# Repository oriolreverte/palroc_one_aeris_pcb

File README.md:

<h1 align="center">aeris_pcb</h1>

<p align="center" width="100%">
  
</p>

***

<p align="center">
  
&nbsp; &nbsp; &nbsp; &nbsp;
  
</p>

***

## SPECIFICATIONS

| Parameter | Value | 
| --- | --- |
| Dimensions | 102.5 × 90.0 mm |

***

## DIRECTORY STRUCTURE

    .
    ├─ Computations       # Misc calculations
    ├─ HTML               # HTML files for generated webpage
    ├─ Images             # Pictures and renders
    │
    ├─ kibot_resources    # External resources for KiBot
    │  ├─ colors          # Color theme for KiCad
    │  ├─ fonts           # Fonts used in the project
    │  ├─ scripts         # External scripts used with KiBot
    │  └─ templates       # Templates for KiBot generated reports
    │
    ├─ kibot_yaml         # KiBot YAML config files
    ├─ KiRI               # KiRI (PCB diff viewer) files
    │
    ├─ lib                # KiCad footprint and symbol libraries
    │  ├─ 3d_models       # Component 3D models
    │  ├─ lib_fp          # Footprint libraries
    │  └─ lib_sym         # Symbol libraries
    │
    ├─ Logos              # Logos
    │
    ├─ Manufacturing      # Assembly and fabrication documents
    │  ├─ Assembly        # Assembly documents (BoM, pos, notes)
    │  │
    │  └─ Fabrication     # Fabrication documents (ZIP, notes)
    │     ├─ Drill Tables # CSV drill tables
    │     └─ Gerbers      # Gerbers
    │
    ├─ Report             # Reports for ERC/DRC
    ├─ Schematic          # PDF of schematic
    ├─ Templates          # Title block templates
    ├─ Testing
    │  └─ Testpoints      # Testpoints tables      
    │
    └─ Variants           # Outputs for assembly variants

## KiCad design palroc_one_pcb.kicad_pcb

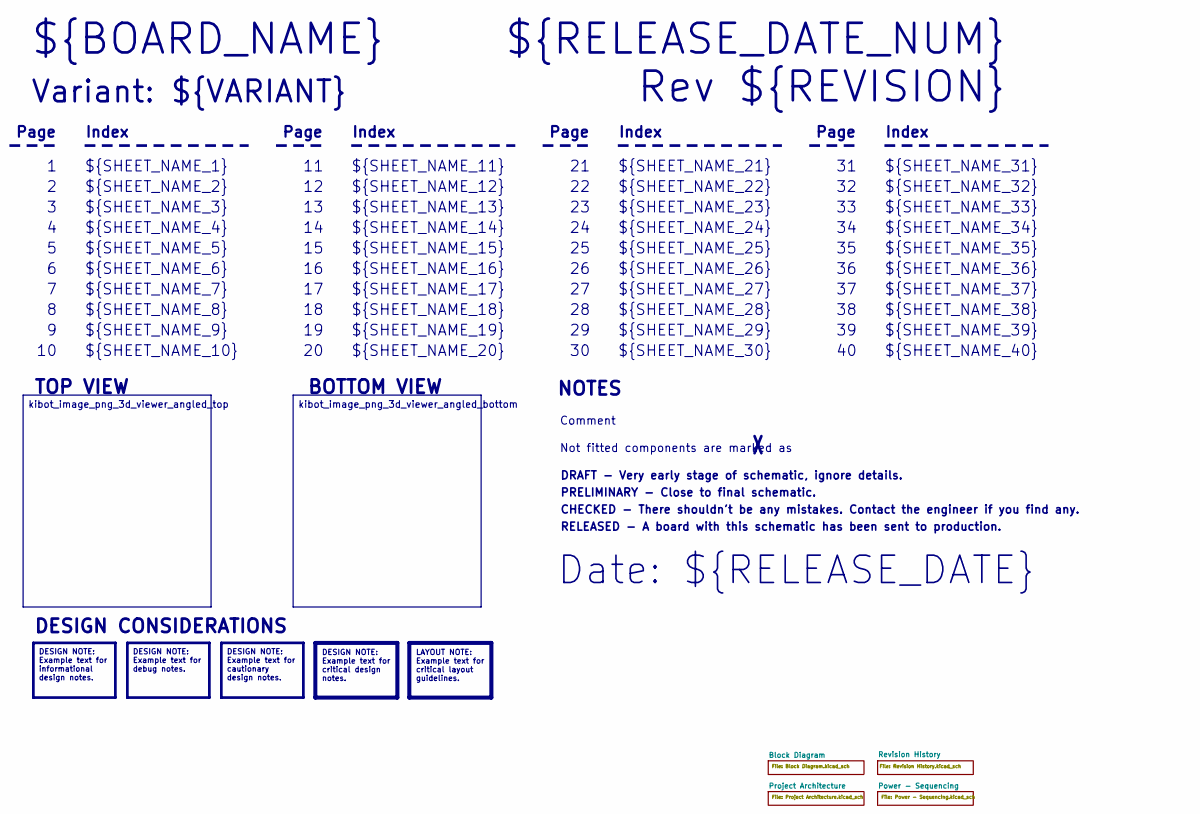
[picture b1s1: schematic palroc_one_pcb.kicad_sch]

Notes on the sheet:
Variant: ${VARIANT}
RELEASED - A board with this schematic has been sent to production.
${SHEET_NAME_24}
Index
Page
PRELIMINARY - Close to final schematic.
${SHEET_NAME_22}
DRAFT - Very early stage of schematic, ignore details.
${SHEET_NAME_12}
${SHEET_NAME_8}
${SHEET_NAME_2}
${SHEET_NAME_5}
${SHEET_NAME_20}
${SHEET_NAME_23}
${RELEASE_DATE_NUM}
${SHEET_NAME_35}
Not fitted components are marked as
${SHEET_NAME_11}
${SHEET_NAME_6}
${SHEET_NAME_37}
${SHEET_NAME_26}
${SHEET_NAME_36}
Rev ${REVISION}
${SHEET_NAME_15}
CHECKED - There shouldn't be any mistakes. Contact the engineer if you find any.
BOTTOM VIEW
${SHEET_NAME_14}
${SHEET_NAME_21}
${SHEET_NAME_17}
${SHEET_NAME_18}
Date: ${RELEASE_DATE}
${SHEET_NAME_7}
${SHEET_NAME_31}
${BOARD_NAME}
NOTES
${SHEET_NAME_40}
${SHEET_NAME_39}
${SHEET_NAME_32}
${SHEET_NAME_1}
${SHEET_NAME_9}

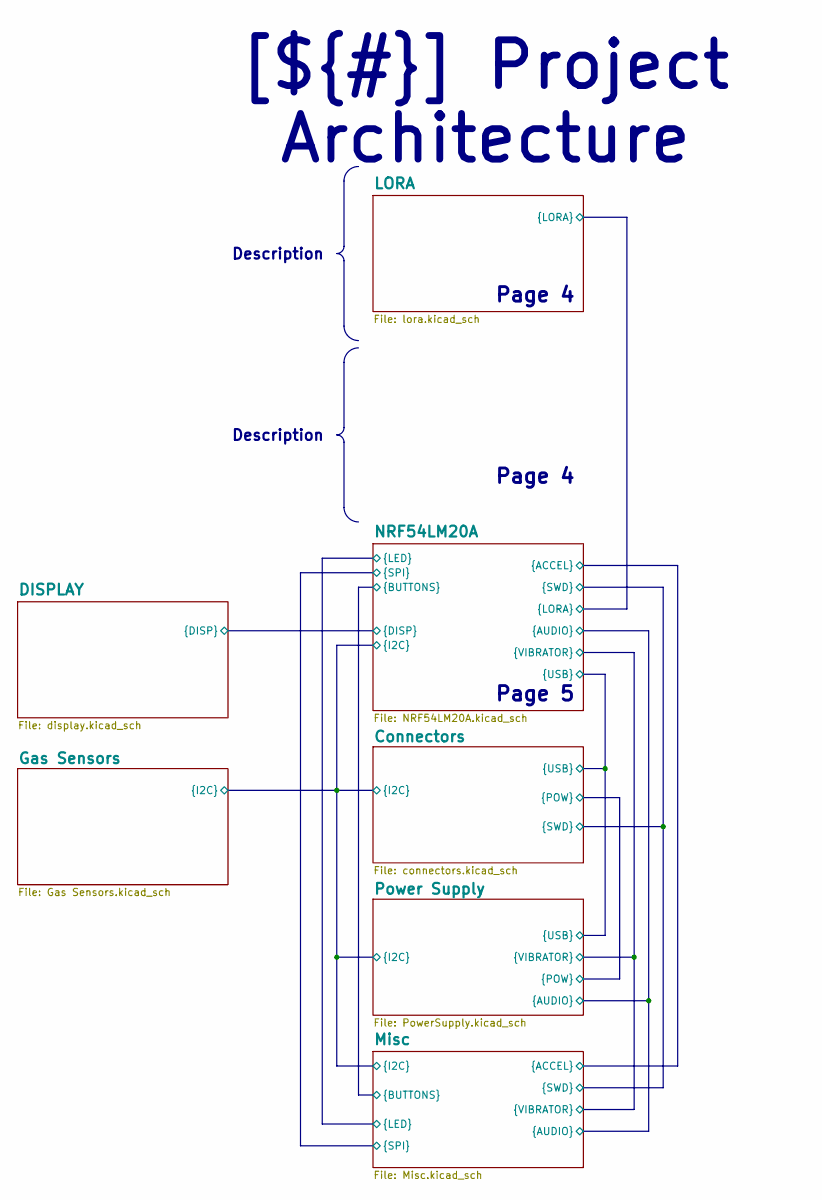
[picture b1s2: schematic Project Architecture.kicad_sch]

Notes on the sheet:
Page 4
Page 5
Description
[${#}] ${TITLE}

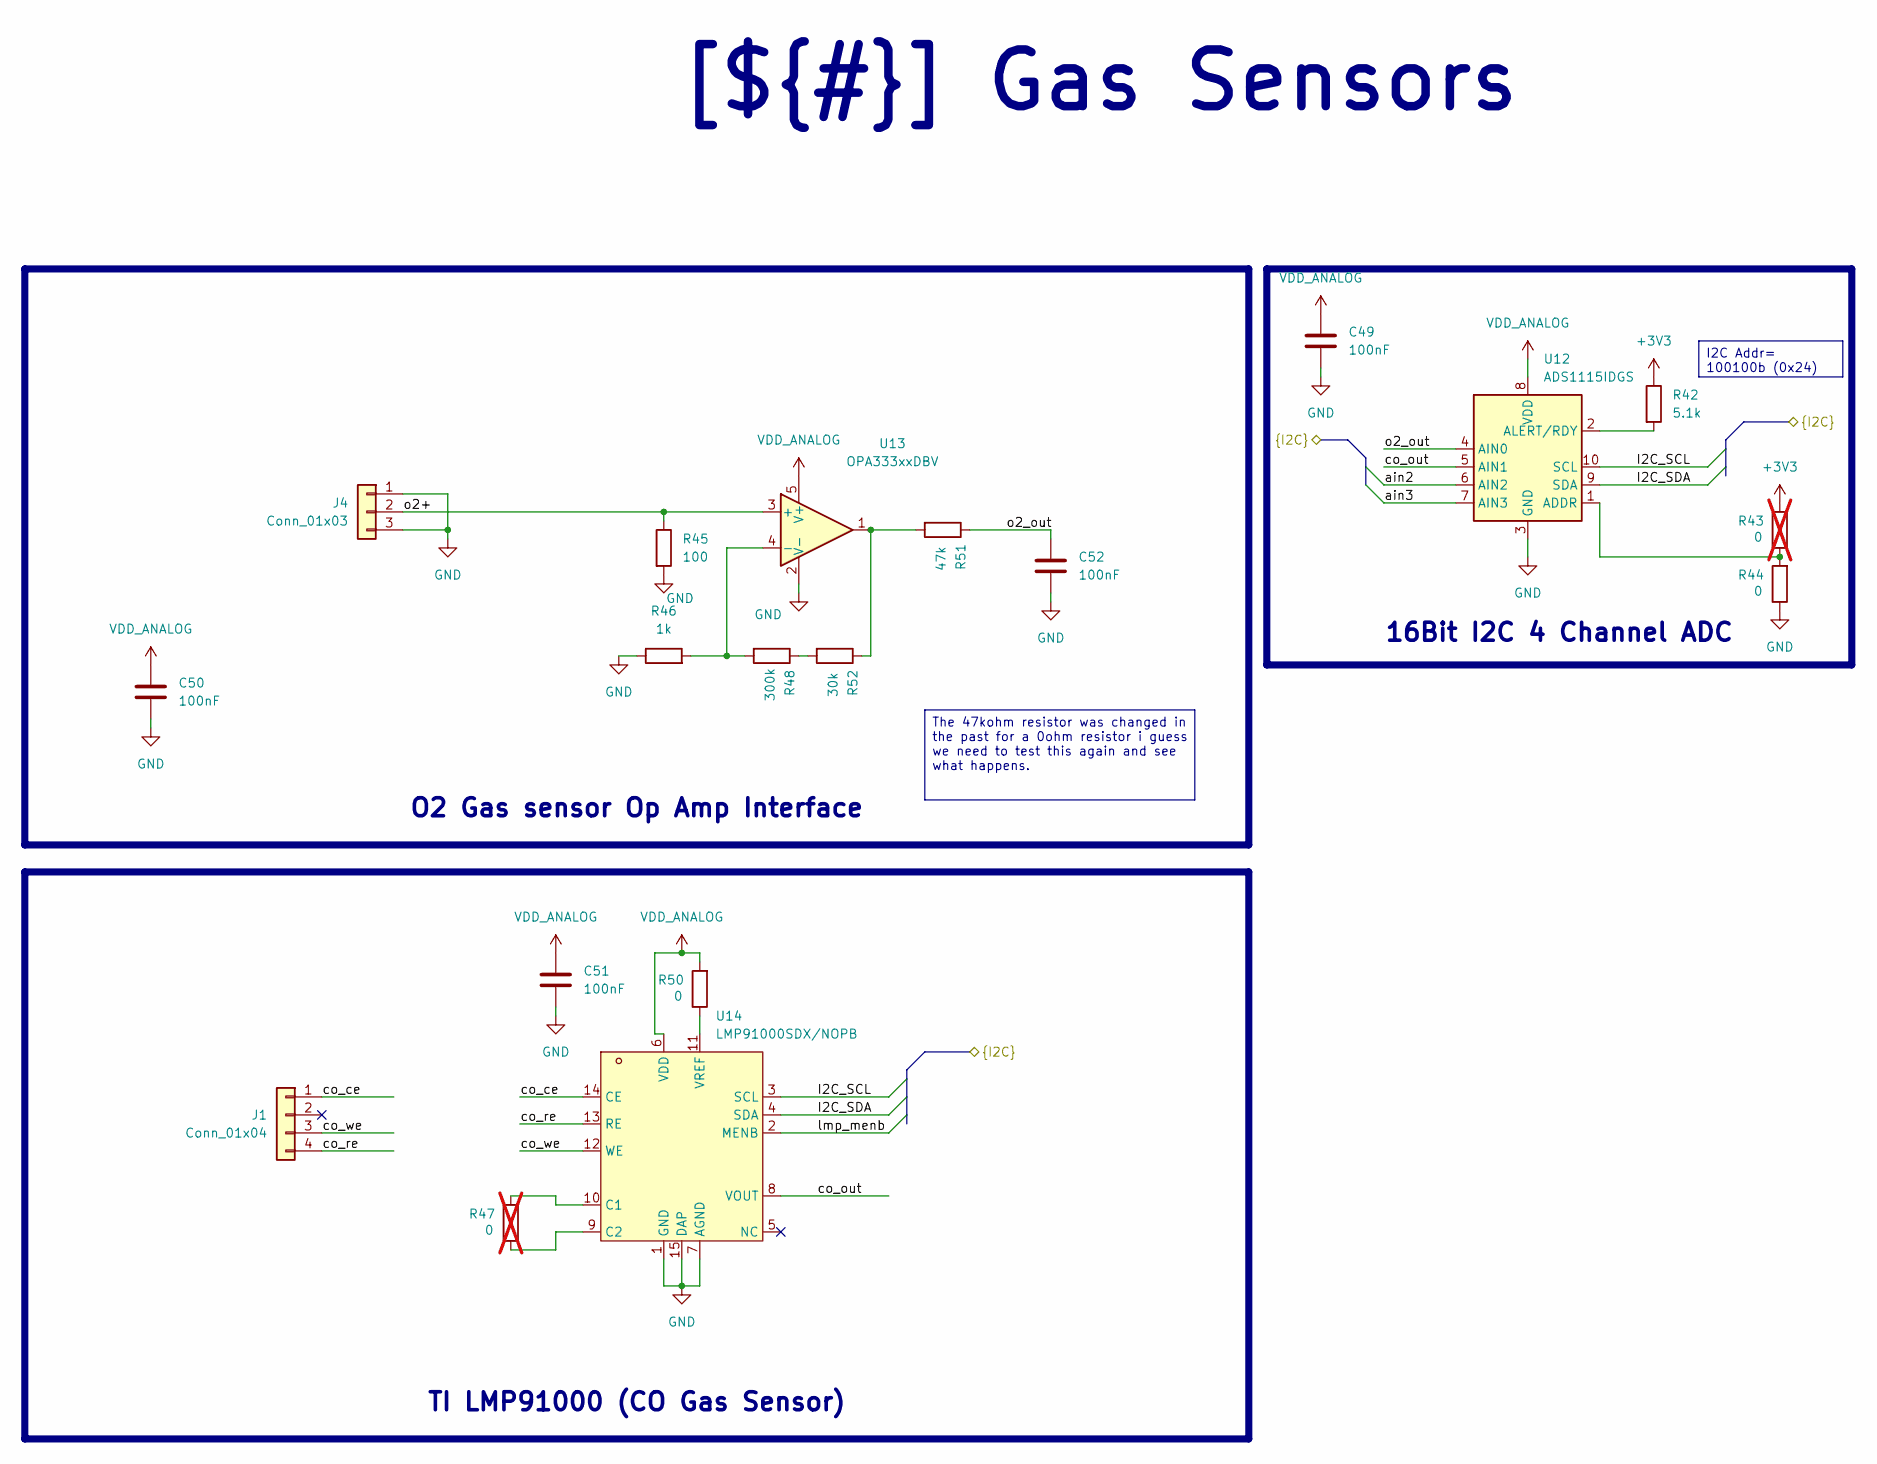
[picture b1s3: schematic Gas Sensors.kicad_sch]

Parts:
C49, C50, C51, C52: 100nF; c_0402_nordic; LCSC C1525
J1: Conn_01x04; 0294-0-15-80-06-80-10-0_co-d4
J4: Conn_01x03; 0364-0-15-80-13-80-10-0_o2-g2
R42: 5.1k; r_0402_nordic; LCSC C25905
R43, R47: 0; r_0402_nordic; Manufacturer Part Number ERJ-2GE0R00X; LCSC C242160; not fitted
R44, R50: 0; r_0402_nordic; Manufacturer Part Number ERJ-2GE0R00X; LCSC C242160
R45: 100; r_0402_nordic; LCSC C25076
R46: 1k; r_0402_nordic; LCSC C11702
R48: 300k; r_0402_nordic; Manufacturer Part Number 0402WGF3003TCE; LCSC C25774
R51: 47k; r_0402_nordic; LCSC C25792
R52: 30k; r_0603_nordic; LCSC C22984
U12: ADS1115IDGS; TSSOP-10_3x3mm_P0.5mm; LCSC C37593
U13: OPA333xxDBV; SOT-23-5
U14: LMP91000SDX/NOPB; WSON-14_L4.0-W4.0-P0.50-BL-EP-1; LCSC Part C2651584

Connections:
+3V3: R42.1, R43.2; also elsewhere on the board
/Project Architecture/Connectors/I2C_SCL: U12.10 (SCL), U14.3 (SCL); also elsewhere on the board
/Project Architecture/Connectors/I2C_SDA: U12.9 (SDA), U14.4 (SDA); also elsewhere on the board
/Project Architecture/Gas Sensors/ain2: U12.6 (AIN2)
/Project Architecture/Gas Sensors/ain3: U12.7 (AIN3)
/Project Architecture/Gas Sensors/co_ce: J1.1, U14.14 (CE)
/Project Architecture/Gas Sensors/co_out: U12.5 (AIN1), U14.8 (VOUT)
/Project Architecture/Gas Sensors/co_re: J1.4, U14.13 (RE)
/Project Architecture/Gas Sensors/co_we: J1.3, U14.12 (WE)
/Project Architecture/Gas Sensors/lmp_menb: U14.2 (MENB)
/Project Architecture/Gas Sensors/o2+: J4.2, R45.1, U13.3 (+)
/Project Architecture/Gas Sensors/o2_out: C52.1, R51.1, U12.4 (AIN0)
GND: C49.2, C50.2, C51.2, C52.2, J4.1, J4.3, R44.1, R45.2, R46.1, U12.3 (GND), U13.2 (V-), U14.1 (GND), U14.7 (AGND), U14.15 (DAP); also elsewhere on the board
unnamed: R48.1, R52.2
unnamed: R51.2, R52.1, U13.1
unnamed: R43.1, R44.2, U12.1 (ADDR)
unnamed: R42.2, U12.2 (ALERT/RDY)
unnamed: R46.2, R48.2, U13.4 (-)
unnamed: R47.2, U14.10 (C1)
unnamed: R47.1, U14.9 (C2)
unnamed: R50.1, U14.11 (VREF)
VDD_ANALOG: C49.1, C50.1, C51.1, R50.2, U12.8 (VDD), U13.5 (V+), U14.6 (VDD); also elsewhere on the board

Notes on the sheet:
16Bit I2C 4 Channel ADC
I2C Addr= 100100b (0x24)
[${#}] ${TITLE}
The 47kohm resistor was changed in the past for a 0ohm resistor i guess we need to test this again and see what happens.
TI LMP91000 (CO Gas Sensor)
O2 Gas sensor Op Amp Interface

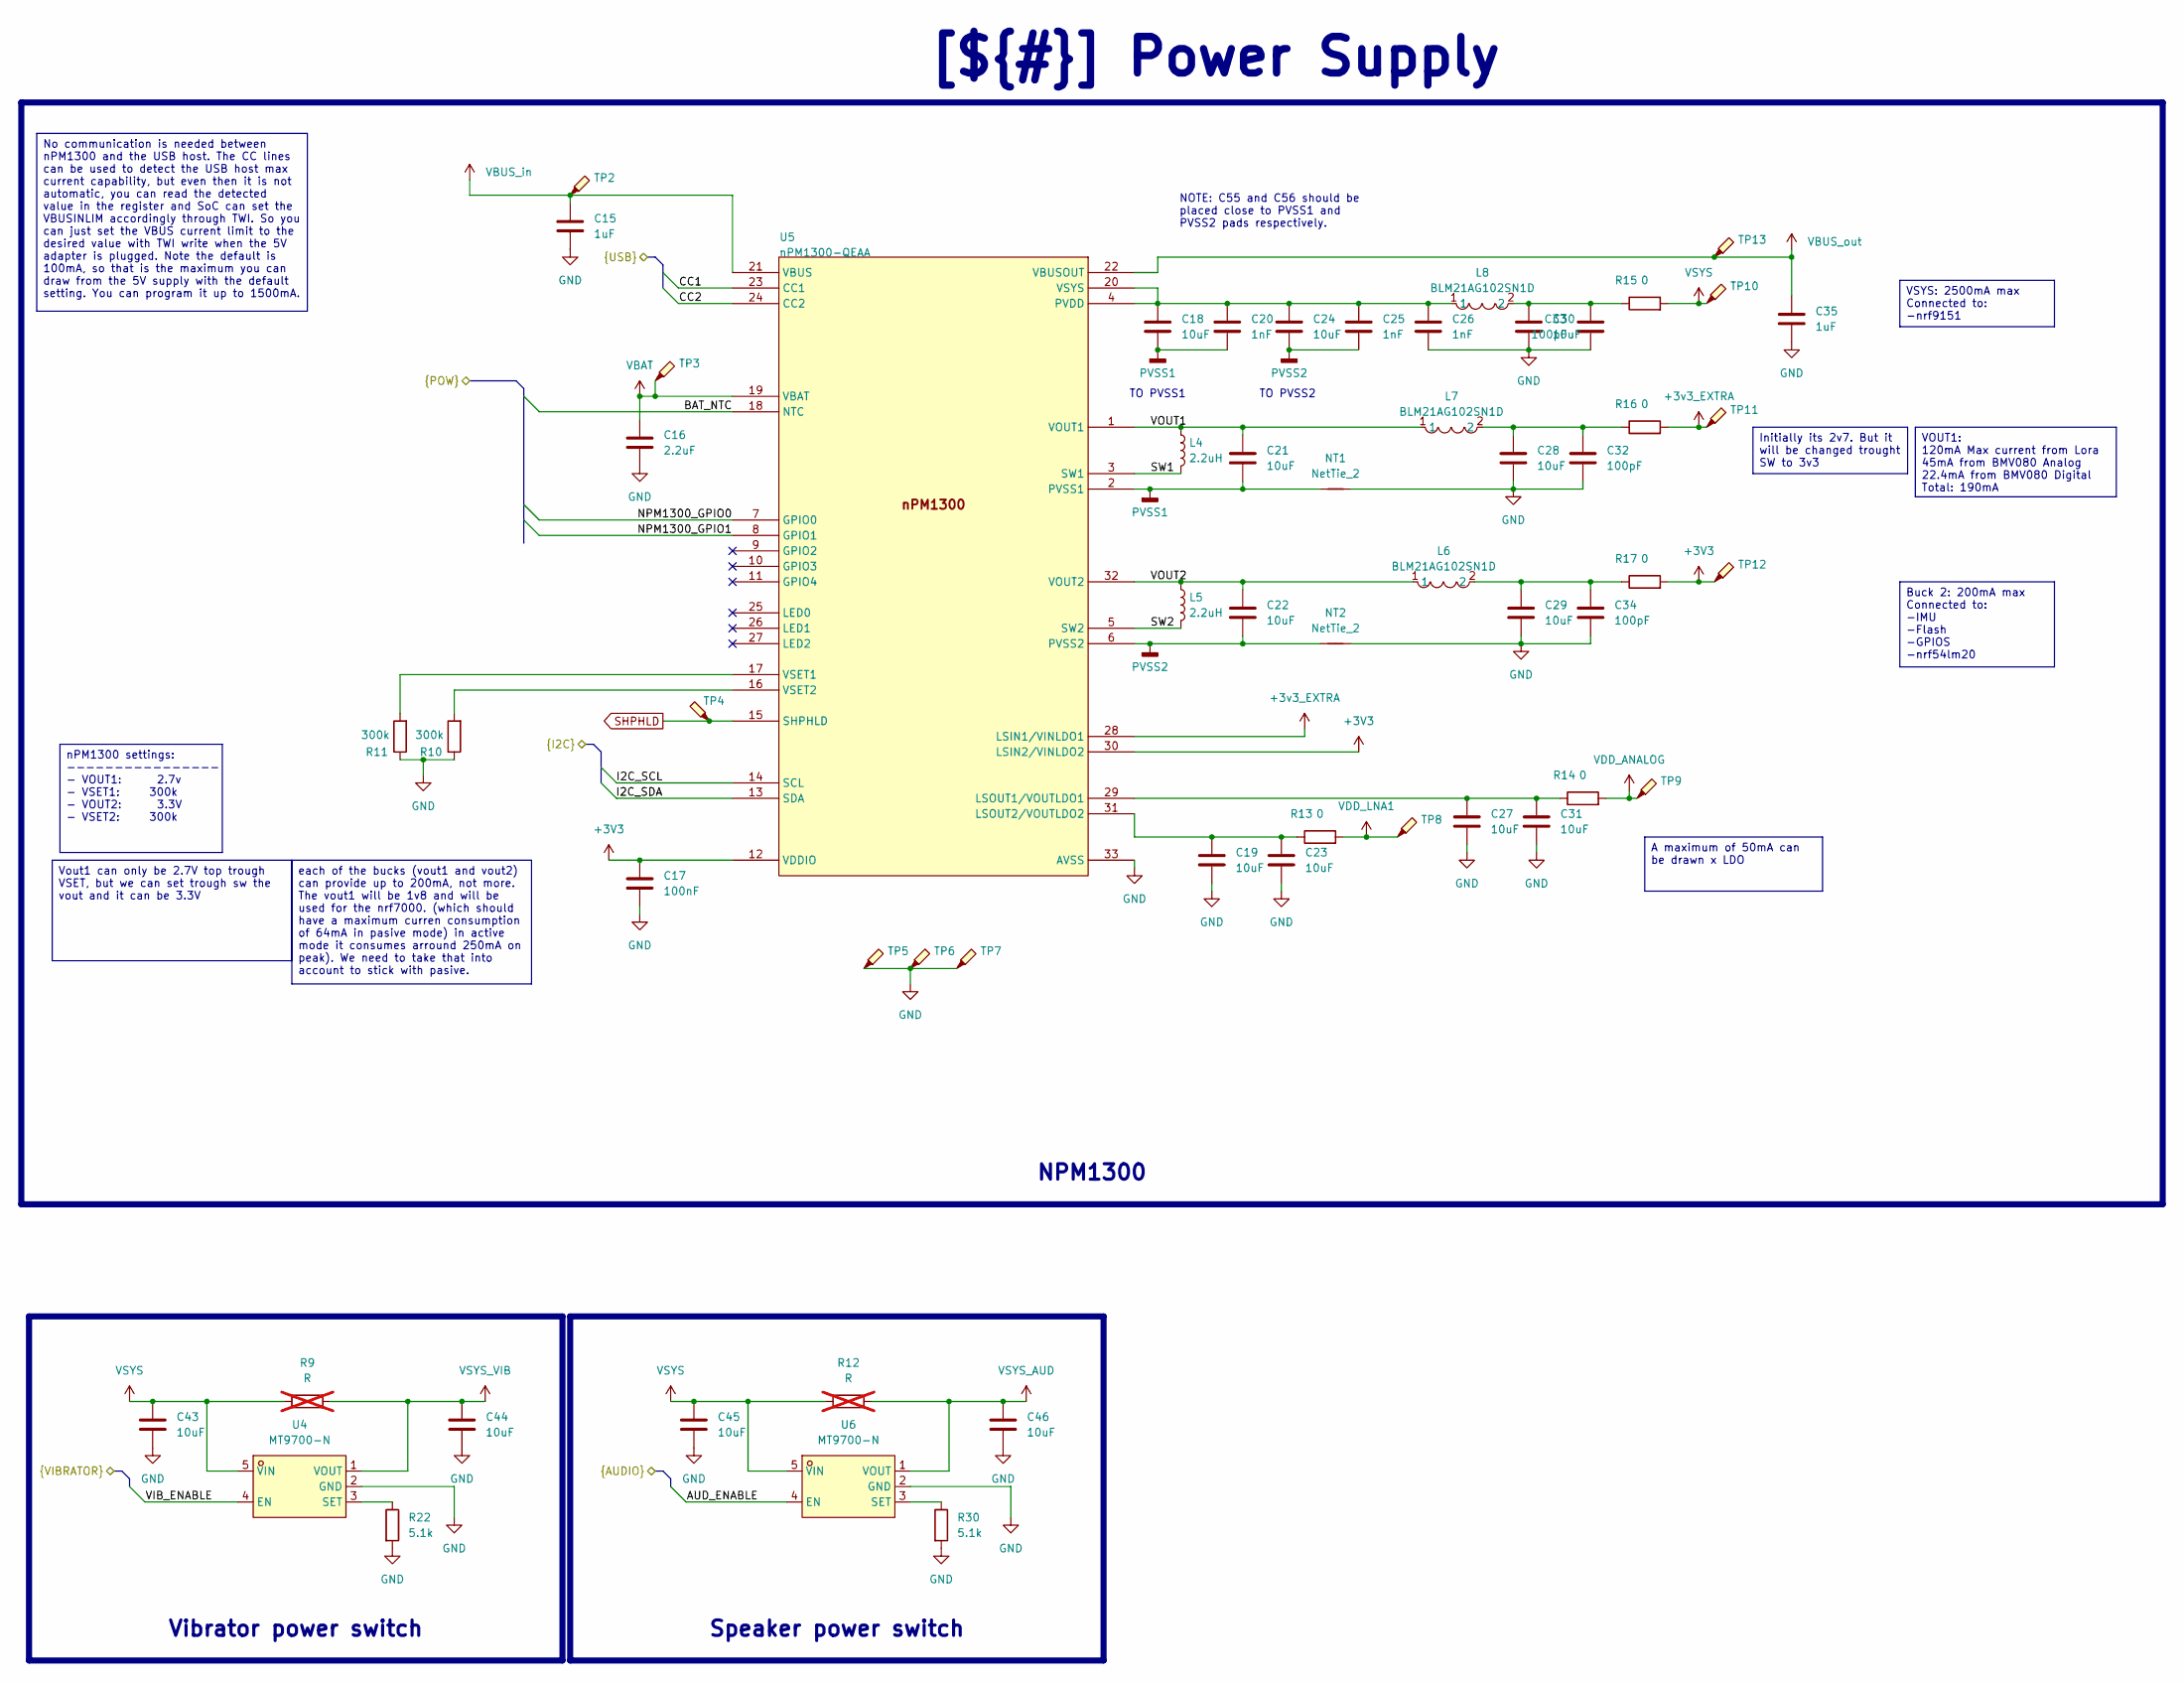
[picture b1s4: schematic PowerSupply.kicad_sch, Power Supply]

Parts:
C15, C35: 1uF; c_0402_nordic; Manufacturer Part Number CL05A105KA5NQNC; LCSC C52923
C16: 2.2uF; c_0402_nordic; Manufacturer Part Number CL05A225KO5NQNC; LCSC C170151
C17: 100nF; c_0201_nordic; Manufacturer Part Number CGA0201X5R104K100ET
C18, C24: 10uF; c_0603_nordic; Manufacturer Part Number CL10A106KP8NNNC; LCSC C19702
C19, C21, C22, C23, C27, C28, C29, C30, C31: 10uF; c_0402_nordic; Manufacturer Part Number CL05A106MP5NUNC; LCSC C315248
C20, C25, C26: 1nF; c_0201_nordic; Manufacturer Part Number CC0201KRX7R8BB102; LCSC C272854
C32, C33, C34: 100pF; c_0201_nordic; Manufacturer Part Number GRM0335C1E101GA01D
C43, C44, C45, C46: 10uF; c_0603_nordic; LCSC C19702
L4, L5: 2.2uH; l_0806_nordic; Manufacturer Part Number DFE201610E-2R2M=P2; LCSC C337891
L6, L7, L8: BLM21AG102SN1D; L0805; LCSC Part C85835
NT1, NT2: NetTie_2; NetTie-PALROC-viamm
R9, R12: R; r_0603_nordic; not fitted
R10, R11: 300k; r_0402_nordic; Manufacturer Part Number 0402WGF3003TCE; LCSC C25774
R13, R14, R15, R16, R17: 0; r_0402_nordic; Manufacturer Part Number ERJ-2GE0R00X; LCSC C242160
R22, R30: 5.1k; r_0402_nordic; LCSC C25905
TP2, TP3, TP4, TP5, TP6, TP7, TP8, TP9, TP10, TP11, TP12, TP13: TestPoint_Probe; TestPoint_Pad_D1.0mm
U4, U6: MT9700-N; SOT-23-5_L2.9-W1.6-P0.95-LS2.9-BL; MPN MT9700-N; LCSC Part C42441843
U5: nPM1300-QEAA; Nordic_QFN50P500X500X90-33N; PART NUMBER nPM1300-QEAA

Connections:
+3V3: C17.1, R17.2, TP12.1, U5.12 (VDDIO), U5.30 (LSIN2/VINLDO2); also elsewhere on the board
+3v3_EXTRA: R16.2, TP11.1, U5.28 (LSIN1/VINLDO1); also elsewhere on the board
/Project Architecture/Connectors/BAT_NTC: U5.18 (NTC); also elsewhere on the board
/Project Architecture/Connectors/CC1: U5.23 (CC1); also elsewhere on the board
/Project Architecture/Connectors/CC2: U5.24 (CC2); also elsewhere on the board
/Project Architecture/Connectors/I2C_SCL: U5.14 (SCL); also elsewhere on the board
/Project Architecture/Connectors/I2C_SDA: U5.13 (SDA); also elsewhere on the board
/Project Architecture/Misc/AUD_ENABLE: U6.4 (EN); also elsewhere on the board
/Project Architecture/Misc/VIB_ENABLE: U4.4 (EN); also elsewhere on the board
/Project Architecture/Power Supply/NPM1300_GPIO0: U5.7 (GPIO0)
/Project Architecture/Power Supply/NPM1300_GPIO1: U5.8 (GPIO1)
/Project Architecture/Power Supply/SW1: L4.2, U5.3 (SW1)
/Project Architecture/Power Supply/SW2: L5.2, U5.5 (SW2)
/Project Architecture/Power Supply/VOUT1: C21.1, L4.1, L7.1, U5.1 (VOUT1)
/Project Architecture/Power Supply/VOUT2: C22.1, L5.1, L6.1, U5.32 (VOUT2)
GND: C15.2, C16.2, C17.2, C19.2, C23.2, C26.2, C27.2, C28.2, C29.2, C30.2, C31.2, C32.2, C33.2, C34.2, C35.2, C43.2, C44.2, C45.2, C46.2, NT1.2, NT2.2, R10.1, R11.1, R22.2, R30.2, TP5.1, TP6.1, TP7.1, U4.2 (GND), U5.33 (AVSS), U6.2 (GND); also elsewhere on the board
unnamed: C28.1, C32.1, L7.2, R16.1
unnamed: C29.1, C34.1, L6.2, R17.1
unnamed: C30.1, C33.1, L8.2, R15.1
unnamed: R22.1, U4.3 (SET)
unnamed: C27.1, C31.1, R14.1, U5.29 (LSOUT1/VOUTLDO1)
unnamed: C19.1, C23.1, R13.1, U5.31 (LSOUT2/VOUTLDO2)
unnamed: C18.1, C20.1, C24.1, C25.1, C26.1, L8.1, U5.4 (PVDD), U5.20 (VSYS)
unnamed: R11.2, U5.17 (VSET1)
unnamed: R10.2, U5.16 (VSET2)
unnamed: R30.1, U6.3 (SET)
PVSS1: C18.2, C20.2, C21.2, NT1.1, U5.2 (PVSS1)
PVSS2: C22.2, C24.2, C25.2, NT2.1, U5.6 (PVSS2)
SHPHLD: TP4.1, U5.15 (SHPHLD); also elsewhere on the board
VBAT: C16.1, TP3.1, U5.19 (VBAT); also elsewhere on the board
VBUS_in: C15.1, TP2.1, U5.21 (VBUS); also elsewhere on the board
VBUS_out: C35.1, TP13.1, U5.22 (VBUSOUT); also elsewhere on the board
VDD_ANALOG: R14.2, TP9.1; also elsewhere on the board
VDD_LNA1: R13.2, TP8.1
VSYS: C43.1, C45.1, R9.1, R12.1, R15.2, TP10.1, U4.5 (VIN), U6.5 (VIN); also elsewhere on the board
VSYS_AUD: C46.1, R12.2, U6.1 (VOUT); also elsewhere on the board
VSYS_VIB: C44.1, R9.2, U4.1 (VOUT); also elsewhere on the board

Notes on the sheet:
TO PVSS1
TO PVSS2
No communication is needed between nPM1300 and the USB host. The CC lines can be used to detect the USB host max current capability, but even then it is not automatic, you can read the detected value in the register and SoC can set the VBUSINLIM accordingly through TWI. So you can just set the VBUS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
[${#}] ${TITLE}
VSYS: 2500mA max Connected to: -nrf9151
VOUT1: 120mA Max current from Lora 45mA from BMV080 Analog 22.4mA from BMV080 Digital Total: 190mA
Initially its 2v7. But it will be changed trought SW to 3v3
NOTE: C55 and C56 should be placed close to PVSS1 and PVSS2 pads respectively.
A maximum of 50mA can be drawn x LDO
Vibrator power switch
Vout1 can only be 2.7V top trough VSET, but we can set trough sw the vout and it can be 3.3V
each of the bucks (vout1 and vout2) can provide up to 200mA, not more. The vout1 will be 1v8 and will be used for the nrf7000. (which should have a maximum curren consumption of 64mA in pasive mode) in active mode it consumes arround 250mA on peak). We need to take that into account to stick with p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
Buck 2: 200mA max Connected to: -IMU -Flash -GPIOS -nrf54lm20
NPM1300
Speaker power switch
nPM1300 settings: ---------------- - VOUT1: 2.7v - VSET1: 300k - VOUT2: 3.3V - VSET2: 300k

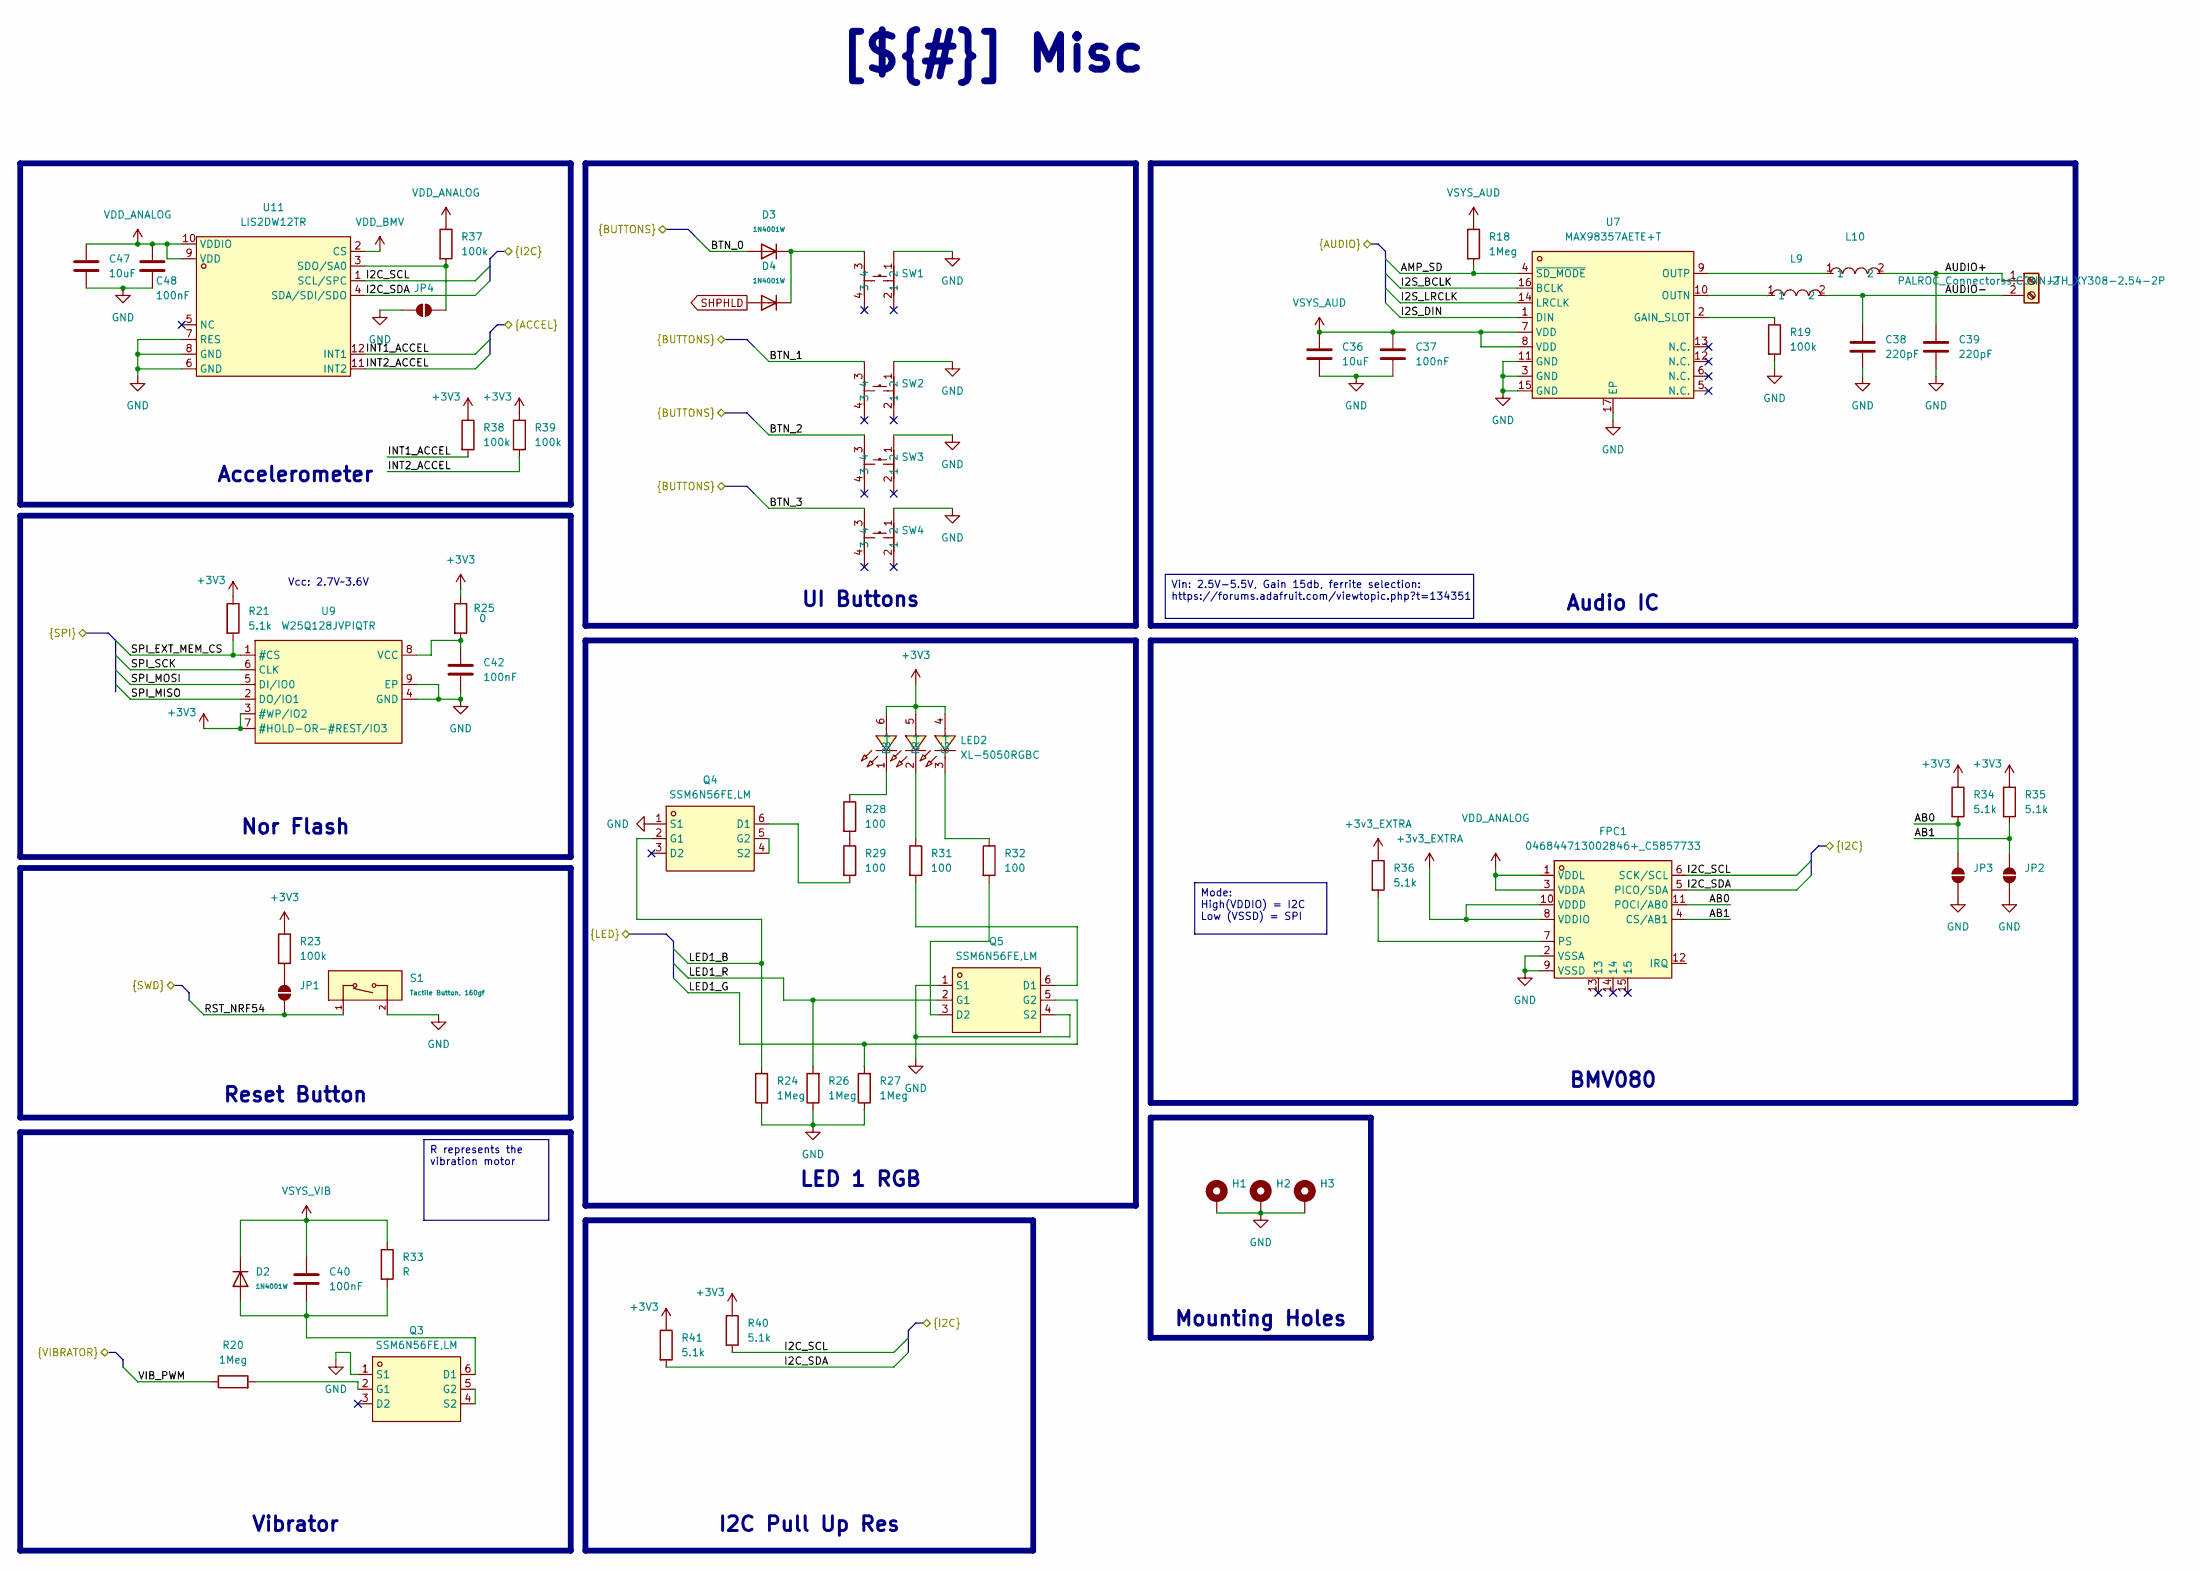
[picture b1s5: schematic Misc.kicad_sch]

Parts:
C36, C47: 10uF; c_0603_nordic; LCSC C19702
C37, C40, C42, C48: 100nF; c_0402_nordic; LCSC C1525
C38, C39: 220pF; c_0402_nordic; MPN 0402B221K500NT; LCSC C1530
D2, D3, D4: 1N4001W; D_SOD-123FL; Voltage - Forward(Vf@If) 1V@1.0A; Voltage - DC Reverse(Vr) 50V; Part 1N4001W; LCSC C18199085
FPC1: 046844713002846+_C5857733; FPC-SMD_13P-P0.60_046844713002846-1; MPN 046844713002846+; LCSC Part C5857733
H1, H2, H3: MountingHole_Pad; MountingHole_2.2mm_M2_DIN965_Pad
J2: Screw_Terminal_01x02; CONN-TH_XY308-2.54-2P
JP1, JP2, JP3, JP4: SolderJumper_2_Open; SolderJumper-2_P1.3mm_Open_RoundedPad1.0x1.5mm
L9, L10: BLM18PG471SN1D; L0603; MPN BLM18PG471SN1D; LCSC Part C97853
LED2: XL-5050RGBC; LED-ARRAY-SMD_6P-L5.0-W5.0-TL-RD_3; MPN XL-5050RGBC; LCSC Part C2843868
Q3, Q4, Q5: SSM6N56FE,LM; ES6_L1.6-W1.2-P0.50-LS1.6-BL; MPN SSM6N56FE,LM; LCSC Part C146449
R18, R20, R24, R26, R27: 1Meg; r_0402_nordic; MPN 0402WGF1004TCE; LCSC C26083
R19, R23, R37, R38, R39: 100k; r_0402_nordic; MPN 0402WGF1003TCE; LCSC C25741
R21, R34, R35, R36, R40, R41: 5.1k; r_0402_nordic; LCSC C25905
R25: 0; r_0402_nordic; Manufacturer Part Number ERJ-2GE0R00X; LCSC C242160
R28, R29, R31, R32: 100; r_0402_nordic; LCSC C25076
R33: R; l_0806_nordic
S1: Tactile Button, 160gf; SW_TS-1088-AR02016; Voltage Rating (Dc) 12V; Part TS-1088-AR02016; LCSC C720477
SW1, SW2, SW3, SW4: ZX-QC66-8.5TP; KEY-SMD_4P-L6.0-W6.0-P4.50-LS8.6_H8.5; MPN ZX-QC66-8.5TP; LCSC Part C7470159
U7: MAX98357AETE+T; TQFN-16_L3.0-W3.0-P0.50-BL-EP1.5; MPN MAX98357AETE+T; LCSC Part C910544
U9: W25Q128JVPIQTR; WSON-8_L6.0-W5.0-P1.27-BL-EP; LCSC Part C190862
U11: LIS2DW12TR; LGA-12_L2.0-W2.0-P0.50-BL; MPN LIS2DW12TR; LCSC Part C189624

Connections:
+3V3: LED2.4 (G+), LED2.5 (R+), LED2.6 (B+), R21.1, R23.1, R25.1, R34.1, R35.1, R38.1, R39.1, R40.1, R41.1, U9.3 (#WP/IO2), U9.7 (#HOLD-OR-#REST/IO3); also elsewhere on the board
+3v3_EXTRA: FPC1.8 (VDDIO), FPC1.10 (VDDD), R36.1; also elsewhere on the board
/Project Architecture/Connectors/I2C_SCL: FPC1.6 (SCK/SCL), R40.2, U11.1 (SCL/SPC); also elsewhere on the board
/Project Architecture/Connectors/I2C_SDA: FPC1.5 (PICO/SDA), R41.2, U11.4 (SDA/SDI/SDO); also elsewhere on the board
/Project Architecture/Connectors/RST_NRF54: JP1.1 (A), S1.1 (A); also elsewhere on the board
/Project Architecture/Misc/AB0: FPC1.11 (POCI/AB0), JP3.2 (B), R34.2
/Project Architecture/Misc/AB1: FPC1.4 (CS/AB1), JP2.2 (B), R35.2
/Project Architecture/Misc/AMP_SD: R18.2, U7.4 (~SD_MODE); also elsewhere on the board
/Project Architecture/Misc/AUDIO+: C39.1, J2.1, L10.2
/Project Architecture/Misc/AUDIO-: C38.1, J2.2, L9.2
/Project Architecture/Misc/BTN_0: D3.2; also elsewhere on the board
/Project Architecture/Misc/BTN_1: SW2.3; also elsewhere on the board
/Project Architecture/Misc/BTN_2: SW3.3; also elsewhere on the board
/Project Architecture/Misc/BTN_3: SW4.3; also elsewhere on the board
/Project Architecture/Misc/I2S_BCLK: U7.16 (BCLK); also elsewhere on the board
/Project Architecture/Misc/I2S_DIN: U7.1 (DIN); also elsewhere on the board
/Project Architecture/Misc/I2S_LRCLK: U7.14 (LRCLK); also elsewhere on the board
/Project Architecture/Misc/INT1_ACCEL: R38.2, U11.12 (INT1); also elsewhere on the board
/Project Architecture/Misc/INT2_ACCEL: R39.2, U11.11 (INT2); also elsewhere on the board
/Project Architecture/Misc/LED1_B: Q4.2 (G1), R24.2; also elsewhere on the board
/Project Architecture/Misc/LED1_G: Q5.5 (G2), R27.2; also elsewhere on the board
/Project Architecture/Misc/LED1_R: Q5.2 (G1), R26.2; also elsewhere on the board
/Project Architecture/Misc/SPI_EXT_MEM_CS: R21.2, U9.1 (#CS); also elsewhere on the board
/Project Architecture/Misc/SPI_MISO: U9.2 (DO/IO1); also elsewhere on the board
/Project Architecture/Misc/SPI_MOSI: U9.5 (DI/IO0); also elsewhere on the board
/Project Architecture/Misc/SPI_SCK: U9.6 (CLK); also elsewhere on the board
/Project Architecture/Misc/VIB_PWM: R20.1; also elsewhere on the board
GND: C36.2, C37.2, C38.2, C39.2, C42.2, C47.2, C48.2, FPC1.2 (VSSA), FPC1.9 (VSSD), H1.1, H2.1, H3.1, JP2.1 (A), JP3.1 (A), JP4.1 (A), Q3.1 (S1), Q4.1 (S1), Q5.1 (S1), Q5.4 (S2), R19.2, R24.1, R26.1, R27.1, S1.2 (B), SW1.1, SW2.1, SW3.1, SW4.1, U7.3 (GND), U7.11 (GND), U7.15 (GND), U7.17 (EP), U9.4 (GND), U9.9 (EP), U11.6 (GND), U11.7 (RES), U11.8 (GND); also elsewhere on the board
unnamed: D3.1, D4.1, SW1.3
unnamed: FPC1.7 (PS), R36.2
unnamed: JP1.2 (B), R23.2
unnamed: JP4.2 (B), R37.2, U11.3 (SDO/SA0)
unnamed: LED2.1 (B-), R28.1
unnamed: LED2.3 (G-), R32.1
unnamed: LED2.2 (R-), R31.1
unnamed: C40.2, D2.2, Q3.6 (D1), R33.2
unnamed: Q3.2 (G1), R20.2
unnamed: Q3.4 (S2), Q3.5 (G2)
unnamed: Q4.6 (D1), R29.2
unnamed: Q4.4 (S2), Q4.5 (G2)
unnamed: Q5.6 (D1), R31.2
unnamed: Q5.3 (D2), R32.2
unnamed: R28.2, R29.1
unnamed: R19.1, U7.2 (GAIN_SLOT)
unnamed: L9.1, U7.10 (OUTN)
unnamed: L10.1, U7.9 (OUTP)
unnamed: C42.1, R25.2, U9.8 (VCC)
SHPHLD: D4.2; also elsewhere on the board
VDD_ANALOG: C47.1, C48.1, FPC1.1 (VDDL), FPC1.3 (VDDA), R37.1, U11.9 (VDD), U11.10 (VDDIO); also elsewhere on the board
VDD_BMV: U11.2 (CS)
VSYS_AUD: C36.1, C37.1, R18.1, U7.7 (VDD), U7.8 (VDD); also elsewhere on the board
VSYS_VIB: C40.1, D2.1, R33.1; also elsewhere on the board

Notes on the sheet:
Vcc: 2.7V~3.6V
LED 1 RGB
UI Buttons
R represents the vibration motor
Vin: 2.5V-5.5V, Gain 15db, ferrite selection: https://forums.adafruit.com/viewtopic.php?t=134351
Mounting Holes
Mode: High(VDDIO) = I2C Low (VSSD) = SPI
Accelerometer
[${#}] ${TITLE}
Nor Flash
Reset Button
Vibrator
I2C Pull Up Res
BMV080
Audio IC

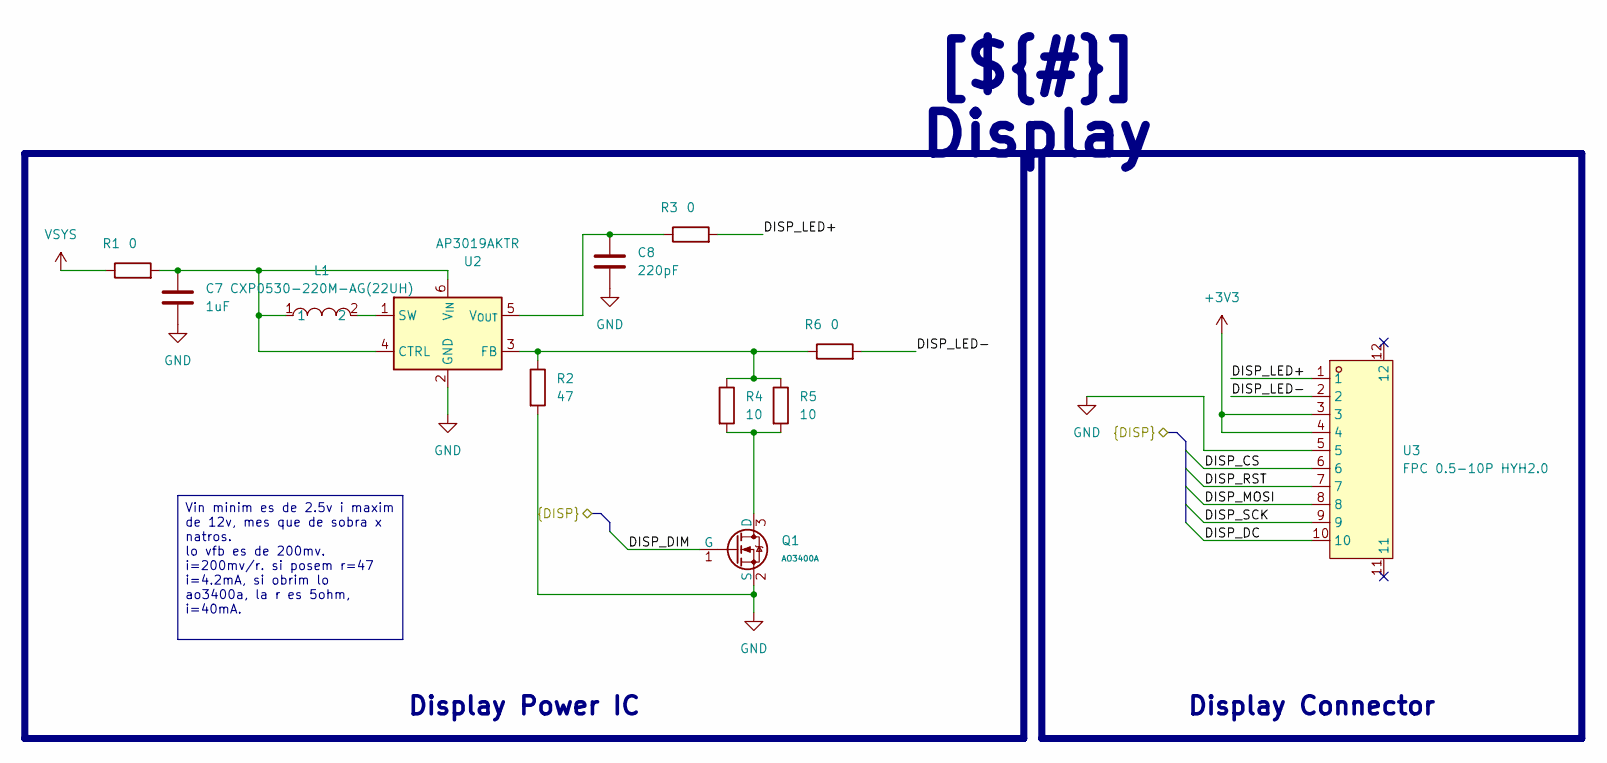
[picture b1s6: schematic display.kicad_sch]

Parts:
C7: 1uF; c_0402_nordic; LCSC C52923
C8: 220pF; c_0402_nordic; MPN 0402B221K500NT; LCSC C1530
L1: CXP0530-220M-AG(22UH); IND-SMD_L5.7-W5.2; LCSC Part C7461351
Q1: AO3400A; Q_SOT-23; Part AO3400A; LCSC C20917
R1, R3, R6: 0; r_0402_nordic; Manufacturer Part Number ERJ-2GE0R00X; LCSC C242160
R2: 47; r_0402_nordic; LCSC C25118
R4, R5: 10; r_0402_nordic; LCSC C25077
U2: AP3019AKTR; SOT-23-6
U3: FPC 0.5-10P HYH2.0; FPC-SMD_10P-P0.50_FPC-0.5-10P-HYH2.0; LCSC Part C6364659

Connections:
+3V3: U3.3, U3.4; also elsewhere on the board
/Project Architecture/DISPLAY/DISP_CS: U3.6; also elsewhere on the board
/Project Architecture/DISPLAY/DISP_DC: U3.10; also elsewhere on the board
/Project Architecture/DISPLAY/DISP_DIM: Q1.1 (G); also elsewhere on the board
/Project Architecture/DISPLAY/DISP_LED+: R3.2, U3.1
/Project Architecture/DISPLAY/DISP_LED-: R6.2, U3.2
/Project Architecture/DISPLAY/DISP_MOSI: U3.8; also elsewhere on the board
/Project Architecture/DISPLAY/DISP_RST: U3.7; also elsewhere on the board
/Project Architecture/DISPLAY/DISP_SCK: U3.9; also elsewhere on the board
GND: C7.2, C8.2, Q1.2 (S), R2.2, U2.2 (GND), U3.5; also elsewhere on the board
unnamed: Q1.3 (D), R4.2, R5.2
unnamed: C7.1, L1.1, R1.2, U2.4 (CTRL), U2.6 (V_{IN})
unnamed: R2.1, R4.1, R5.1, R6.1, U2.3 (FB)
unnamed: L1.2, U2.1 (SW)
unnamed: C8.1, R3.1, U2.5 (V_{OUT})
VSYS: R1.1; also elsewhere on the board

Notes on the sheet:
[${#}] ${TITLE}
Display Power IC
Vin minim es de 2.5v i maxim de 12v, mes que de sobra x natros. lo vfb es de 200mv. i=200mv/r. si posem r=47 i=4.2mA, si obrim lo ao3400a, la r es 5ohm, i=40mA.
Display Connector
